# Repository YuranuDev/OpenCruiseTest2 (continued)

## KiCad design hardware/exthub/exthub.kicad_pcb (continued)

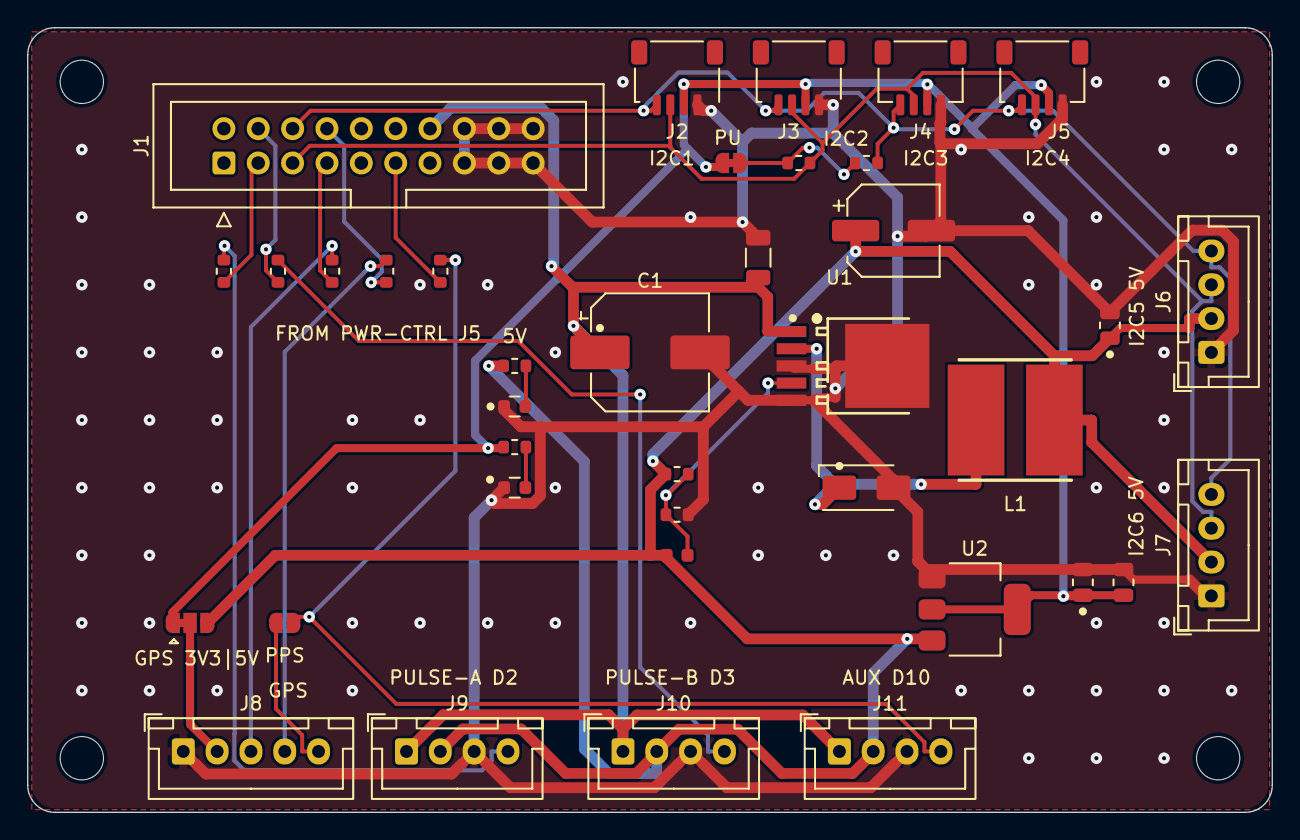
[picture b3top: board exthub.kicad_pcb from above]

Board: 2 copper layers, 92.0 x 58.0 mm, 42 parts (0 on the bottom side), 23 nets.

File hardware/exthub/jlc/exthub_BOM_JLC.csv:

Comment,Designator,Footprint,LCSC Part #
100uF/50V,"C1",CP_Elec_8x10.5,C48935390
1uF/50V,"C2",C_1206_3216Metric,C1848
100uF/16V,"C3",CP_Elec_6.3x5.4,C2887276
10uF/25V,"C4,C6,C7",C_0805_2012Metric,C15850
33nF,"C5",C_0603_1608Metric,C106856
SS34,"D1",D_SMA,C8678
LED 5V (red),"D2",LED_0603_1608Metric,C2286
LED 3V3 (red),"D3",LED_0603_1608Metric,C2286
100uH/1A,"L1",L_8040_SWPA8040,C83468
100,"R1,R2,R3,R4,R5",R_0603_1608Metric,C22775
10.7k,"R6",R_0603_1608Metric,C5153968
3.3k,"R7",R_0603_1608Metric,C22978
1k,"R8,R9",R_0603_1608Metric,C21190
2.7k,"R10,R11",R_0603_1608Metric,C13167
XL7015E1,"U1",TO-252-5_XL7015,C73013
AMS1117-3.3,"U2",SOT-223-3_TabPin2,C6186
